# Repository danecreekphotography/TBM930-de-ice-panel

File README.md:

# TBM930 de-ice panel PCB

This PCB implements a TBM930 de-ice panel for use with Microsoft Flight Simulator
2020 and [MobiFlight](http://www.mobiflight.com/).

## KiBot automation

This repo also demonstrates using KiBot for full CI/CD of KiCad projects. Every pull request gets ERC/DRC checks.
Publishing a GitHub release triggers generation of a suite of PCB documentation, interactive BOM, and submission
files for JLCPCB (including pick-and-place files) and PCBWay. The GitHub release version is inserted into the
generated documentation and gerber files as well. A manually triggered workflow to generate documentation is also
included.

Want to use KiBot GitHub automation with your own project? Check out my [GitHub repository template](https://github.com/neilenns/KiBot-CICD-Template/) for KiCad CI/CD to get started!

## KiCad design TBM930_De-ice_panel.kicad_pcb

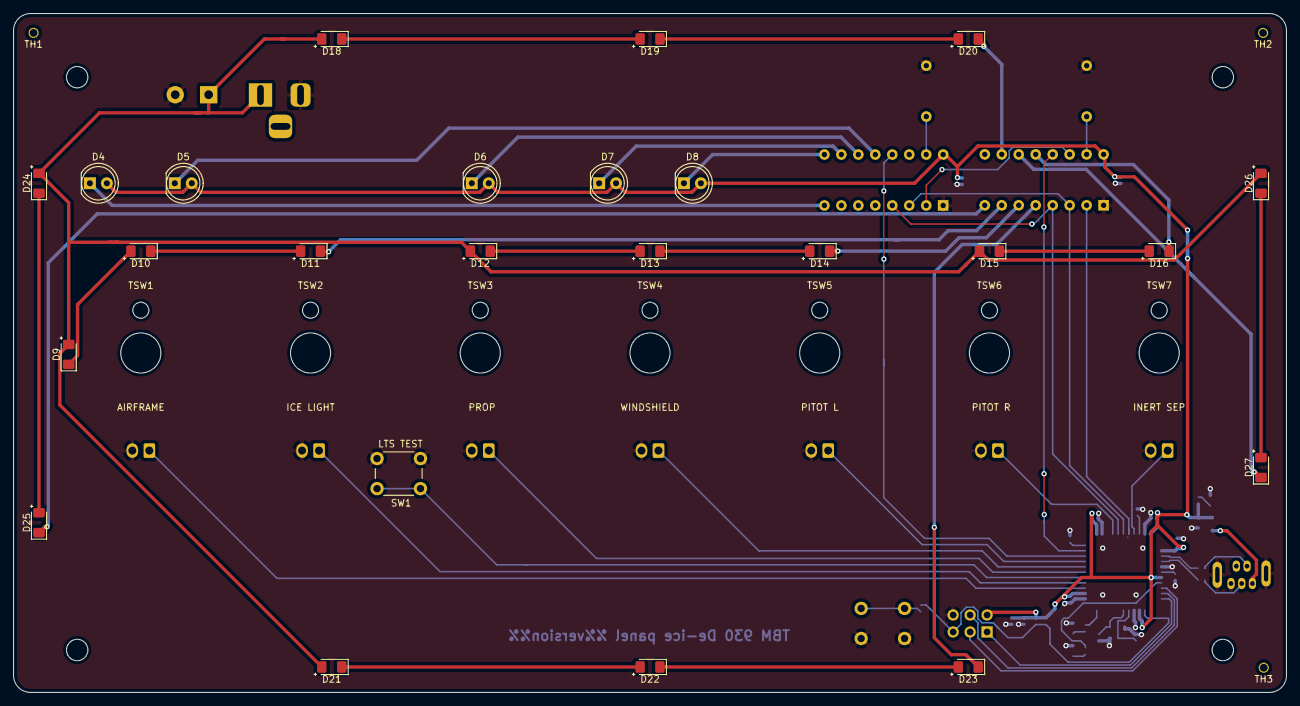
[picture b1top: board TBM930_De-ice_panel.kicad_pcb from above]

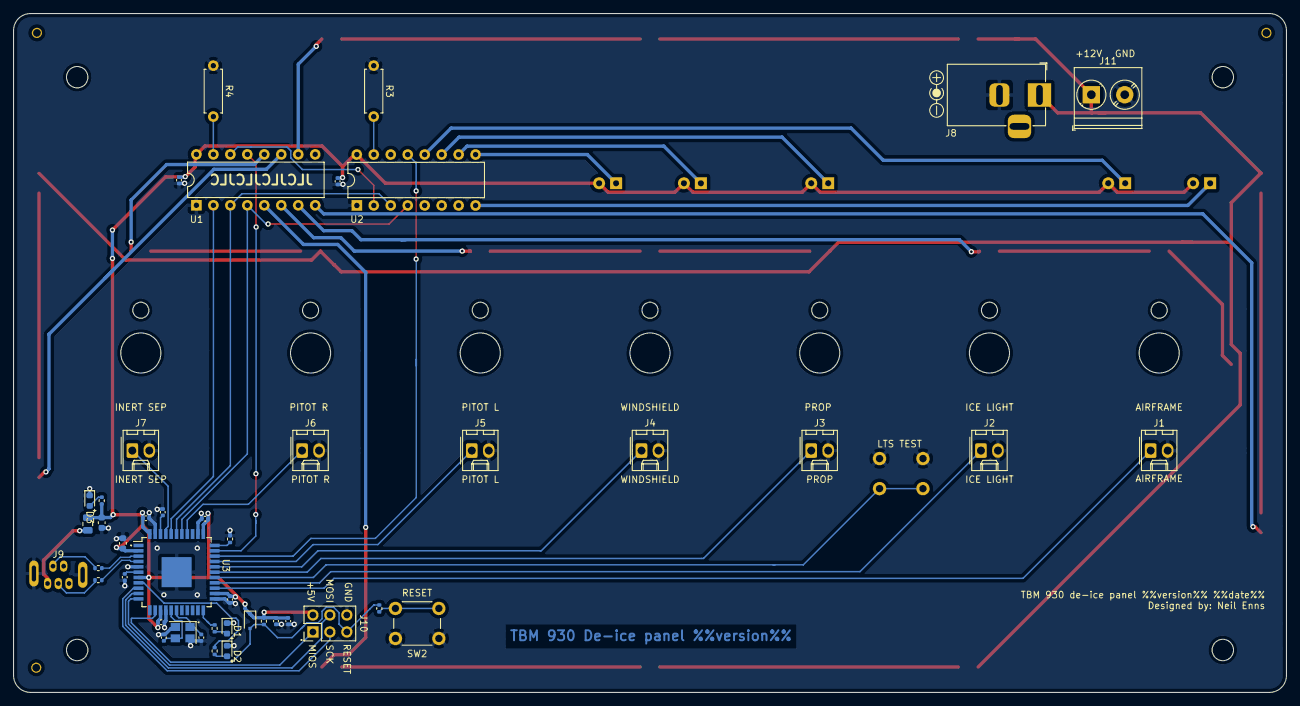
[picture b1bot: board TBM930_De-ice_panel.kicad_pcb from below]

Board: 2 copper layers, 190.5 x 101.6 mm, 83 parts (45 on the bottom side), 62 nets.

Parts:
C1, C10: 10uF; C_0603_1608Metric
C2, C3, C4, C5, C8, C9, C11, C12: 100nf; C_0402_1005Metric
C6, C7: 1uF; C_0402_1005Metric
C16, C17: 20pf; C_0402_1005Metric
D1: YELLOW; LED_0603_1608Metric
D2, D3: GREEN; LED_0603_1608Metric
D4: AIRFRAME 1; LED_D5.0mm
D5: AIRFRAME 2; LED_D5.0mm
D6: PROP; LED_D5.0mm
D7: WINDSHIELD 1; LED_D5.0mm
D8: WINDSHIELD 2; LED_D5.0mm
D9, D10, D11, D12, D13, D14, D15, D16, D18, D19, D20, D21, D22, D23, D24, D25, D26, D27: LED; LED_1206_3216Metric_Pad1.42x1.75mm_HandSolder
D17: D; D_SOD-323F
FB1: Ferrite_Bead_Small; C_0805_2012Metric
HOLE1, HOLE2, HOLE3, HOLE4: MountingHole; MountingHole_3.2mm_M3
J1: SW_AIRFRAME_DE_ICE; Molex_KK-254_AE-6410-02A_1x02_P2.54mm_Vertical
J2: SW_ICE_LIGHT; Molex_KK-254_AE-6410-02A_1x02_P2.54mm_Vertical
J3: SW_PROP_DE_ICE; Molex_KK-254_AE-6410-02A_1x02_P2.54mm_Vertical
J4: SW_WIND_SHIELD; Molex_KK-254_AE-6410-02A_1x02_P2.54mm_Vertical
J5: SW_PITOT_L_HTR; Molex_KK-254_AE-6410-02A_1x02_P2.54mm_Vertical
J6: SW_PITOT_R_HTR; Molex_KK-254_AE-6410-02A_1x02_P2.54mm_Vertical
J7: SW_INERT_SEP; Molex_KK-254_AE-6410-02A_1x02_P2.54mm_Vertical
J8: Barrel_Jack; BarrelJack_Horizontal
J9: USB_B_Mini; USB_B_Mini_Amphenol_UE25BE5510H
J10: AVR-ISP-6; PinHeader_2x03_P2.54mm_Vertical
J11: Screw_Terminal_01x02; TerminalBlock_Phoenix_PT-1,5-2-5.0-H_1x02_P5.00mm_Horizontal
R2, R5, R9: 330; R_0402_1005Metric
R3, R4: 1k; R_Axial_DIN0207_L6.3mm_D2.5mm_P7.62mm_Horizontal
R6: 1K; R_0402_1005Metric
R7, R8: 22; R_0402_1005Metric
R10, R11: 10K; R_0402_1005Metric
SW1: SW_Push; SW_PUSH_6mm_H9.5mm
SW2: SW_Push; SW_PUSH_6mm_H4.3mm
TH1, TH2, TH3: MountingHole; JLCPCB_Tooling_Hole
TSW1, TSW2, TSW3, TSW4, TSW5, TSW6, TSW7: MountingHole; MiniToggleSPDT_screw_mount
U1, U2: TLC5917IN; DIP-16_W7.62mm
U3: ATmega32U4-MU; TQFP-44-1EP_10x10mm_P0.8mm_EP4.5x4.5mm
Y1: Crystal_GND24; Crystal_SMD_3225-4Pin_3.2x2.5mm

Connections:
+5V: C1.1, C2.1, C3.1, C4.1, C5.1, C8.2, C9.2, C10.1, C11.1, C12.1, D4.2, D5.2, D6.2, D7.2, D8.2, D17.1, FB1.1, J10.2, R6.1, R10.1, U1.16, U2.16, U3.2, U3.7, U3.14, U3.24, U3.34, U3.44
+12V_LED: D9.2, D12.2, D15.2, D18.2, D21.2, D24.2, D26.2, J8.1, J11.1
/D17: R2.1, U3.8
/D+: R7.2, U3.4
/D-: R8.2, U3.3
/DR+: J9.3, R7.1
/DR-: J9.2, R8.1
/MISO: J10.1, U3.11
/MOSI: J10.4, U3.10
/SCK: J10.3, U3.9
/VBUS: FB1.2, J9.1
/XTAL1: C16.1, U3.17, Y1.1
/XTAL2: C17.1, U3.16, Y1.3
AIRFRAME_1: D4.1, U2.8
AIRFRAME_2: D5.1, U2.12
BACKLIGHT1: D11.1, U1.7
BACKLIGHT2: D14.1, U1.6
BACKLIGHT3: D16.1, U1.12
BACKLIGHT4: D20.1, U1.10
BACKLIGHT5: D23.1, U1.5
BACKLIGHT6: D25.1, U1.8
BACKLIGHT7: D27.1, U1.11
BACKLIGHT_BRIGHT: U1.13, U3.32
GND: C1.2, C2.2, C3.2, C4.2, C5.2, C6.2, C7.2, C8.1, C9.1, C10.2, C11.2, C12.2, C16.2, C17.2, D1.1, D2.1, D3.1, J1.2, J2.2, J3.2, J4.2, J5.2, J6.2, J7.2, J8.2, J9.5, J9.6, J10.6, J11.2, R3.1, R4.1, R11.2, SW1.1, SW2.2, U1.1, U2.1, U3.5, U3.15, U3.23, U3.35, U3.43, U3.45, Y1.2, Y1.4
INDICATOR_BRIGHT: U2.13, U3.31
LED_CLOCK: U1.3, U2.3, U3.39
LED_DATA: U1.2, U3.40
LED_LATCH: U1.4, U2.4, U3.38
unnamed: C6.1, U3.42
unnamed: C7.1, U3.6
unnamed: D1.2, R2.2
unnamed: D2.2, R5.1
unnamed: D3.2, R6.2
unnamed: D10.1, D11.2
unnamed: D9.1, D10.2
unnamed: D12.1, D13.2
unnamed: D13.1, D14.2
unnamed: D15.1, D16.2
unnamed: D18.1, D19.2
unnamed: D19.1, D20.2
unnamed: D21.1, D22.2
unnamed: D22.1, D23.2
unnamed: D24.1, D25.2
unnamed: D26.1, D27.2
unnamed: R3.2, U2.15
unnamed: R4.2, U1.15
unnamed: R5.2, U3.22
unnamed: R9.1, SW2.1
unnamed: R11.1, U3.33
unnamed: U1.14, U2.2
PROP: D6.1, U2.11
RESET: D17.2, J10.5, R9.2, R10.2, U3.13
SW_AIRFRAME: J1.1, U3.25
SW_ICE_LIGHT: J2.1, U3.26
SW_INERT_SEP: J7.1, U3.41
SW_LTS_TEST: SW1.2, U3.27
SW_PITOT_L: J5.1, U3.30
SW_PITOT_R: J6.1, U3.37
SW_PROP: J3.1, U3.28
SW_WINDSHIELD: J4.1, U3.29
WINDSHIELD_1: D7.1, U2.10
WINDSHIELD_2: D8.1, U2.9

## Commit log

2021-09-18 Initial version
2021-09-18 Fix descriptions and paths
2021-09-18 Add pull request to release.yml for testing
2021-09-18 Trying again to trigger on pull request
2021-09-18 Fix job name
2021-09-18 Trying substitution again
2021-09-18 Remove single quote
2021-09-18 Try and fix folder structure
2021-09-18 Trying again to exclude files
2021-09-18 Trying wildcard change to flatten folder
2021-09-18 Trying again to flatten folder structure
2021-09-18 Gonna try doing a release!
2021-09-18 Initial version (#1)
    * Initial version
    * Fix descriptions and paths
    * Fix descriptions and paths
    * Add pull request to release.yml for testing
    * Trying again to trigger on pull request
    * Fix job name
2021-09-18 Try again on releases
2021-09-18 Try fixing release
2021-09-18 Try fixing release (#2)
2021-09-18 Add zipping release files
2021-09-18 Switch to env variables, zip the release
2021-09-18 Switch to env variables, zip the release (#3)
2021-09-18 Fix broken env in release script
2021-09-19 Try removing multi-level folder structure
2021-09-19 Fix zip line
2021-09-19 Try fixing the zip file AGAIN
2021-09-19 Try different escape sequence for zip
2021-09-19 Try AGAIN to fix the folder
2021-09-19 Trying zip fix again with working directory
2021-09-19 Try folder fix again
2021-09-19 Try fixing permission denied error
2021-09-19 Split docs and JLCPCB zips
2021-09-19 Fix missing BOM files
2021-09-19 Set version in PCB as well
2021-09-19 Fix typo in JLC BOM zip
2021-09-19 Fix switches back to ground connection
2021-09-19 Fix switches back to ground connection (#4)
2021-09-19 Add PCBWay, clean up some names
2021-09-19 Fix case of filename
2021-09-19 Fix PCBWay upload, add MobiFlight config
2021-09-19 Remove unnecessary .gitignore
2021-09-19 Rename zip file
2021-09-19 Attempt 3D model
2021-09-19 Add remote containers as a recommended extension.
2021-09-19 Add VSCode task to run kibot
2021-09-19 Add note about remote container development
2021-09-20 Fix output name for white PCB renders
2021-09-20 Test date output
2021-09-20 Try again
2021-09-20 Change time format
2021-09-20 Renaming for clarity
2021-09-20 Try setting the timezone
2021-09-20 Test timezone again
2021-09-20 Add date test to preflight
2021-09-20 Trying again
2021-09-20 Add quotes
2021-09-20 Fix timezone name
2021-09-20 Update schematic and PCB to use date
2021-09-20 Update build and release to replace date
2021-09-20 Test date output (#5)
    * Test date output
    * Try again
    * Change time format
    * Renaming for clarity
    * Try setting the timezone
    * Test timezone again
2021-09-20 Remove extra quotes
2021-09-20 Date stamp (#6)
    * Test date output
    * Try again
    * Change time format
    * Renaming for clarity
    * Try setting the timezone
    * Test timezone again
2021-09-20 Fix date placeholder on PCB
2021-09-20 Add a ton of documentation and clarification
2021-09-20 Add a ton of documentation and clarification (#7)
2021-09-20 Add code tour
2021-09-20 Add codetour as recommended extension
2021-09-20 Add a code tour (#8)
    * Add code tour
    * Add codetour as recommended extension
2021-09-20 Try different find/replace
2021-09-20 Revert "Try different find/replace"
    This reverts commit 871c726105e5bf8568bb31d38822249d31069fc8.
2021-09-20 Try date replacement
2021-09-20 Trying different regex
2021-09-20 Temporarily package the artifacts
2021-09-20 Testing some more
2021-09-20 Fix error
2021-09-20 Try spitting out count of modified files
2021-09-20 Fix typo
2021-09-20 Find/replace for multiple .sch files
2021-09-20 Support multiple .sch files (#9)
    * Try date replacement
    * Trying different regex
    * Temporarily package the artifacts
    * Testing some more
    * Trying again
    * Fix error
2021-09-20 Replace (#10)
    * Try date replacement
    * Trying different regex
    * Temporarily package the artifacts
    * Testing some more
    * Trying again
    * Fix error
2021-09-20 Test a subsheet
2021-09-20 Test a subsheet (#11)
2021-09-20 Fix timeout errors and make warnings errors?
2021-09-20 Add timeout to preflight
2021-09-20 Add wildcard to preflight
2021-09-20 Temporarily disable ERC in release action
2021-09-20 Get rid of wildcard from KiBot call
2021-09-20 Upload artifacts
2021-09-21 Remove subsheet
2021-09-21 Upload artifacts (#13)
    * Upload artifacts
    * Remove subsheet
    * Remove subsheet
2021-09-21 Test subsheets
2021-09-21 Rename subsheet
2021-09-29 Initial attempt
2021-09-29 Initial attempt (#16)
2021-09-29 Remove getting the github release
2021-09-29 Get rid of github release step (#17)
    * Initial attempt
    * Remove getting the github release
2021-09-29 Remove incorrect filter
2021-09-29 Rename stuff, clean up comments
2021-09-29 Pull version from workflow UI
2021-09-29 Don't do ERC/DRC runs
2021-09-29 Update the codetours
2021-09-29 Update the readme
2021-09-29 Update the codetour (#18)
    * Don't do ERC/DRC runs
    * Update the codetours
    * Update the readme
2021-10-01 Remove stray env variable for version that doesn't apply to this flow
2021-10-02 Add info on how to set up vscode remote containers
2021-10-05 reset author
2021-10-06 Fix email
2021-10-07 Update github actions
2021-10-07 Update to new kibot build (#20)
    * reset author
    * Fix email
    * Update github actions
2021-10-07 Force v1 of find/replace
2021-10-07 Add photo of completed PCB
2021-11-11 Update to new generic KiBot workflows
2021-11-11 Update the codetour
2022-01-20 Add MF board configuration file
2025-02-25 Add renovate.json
